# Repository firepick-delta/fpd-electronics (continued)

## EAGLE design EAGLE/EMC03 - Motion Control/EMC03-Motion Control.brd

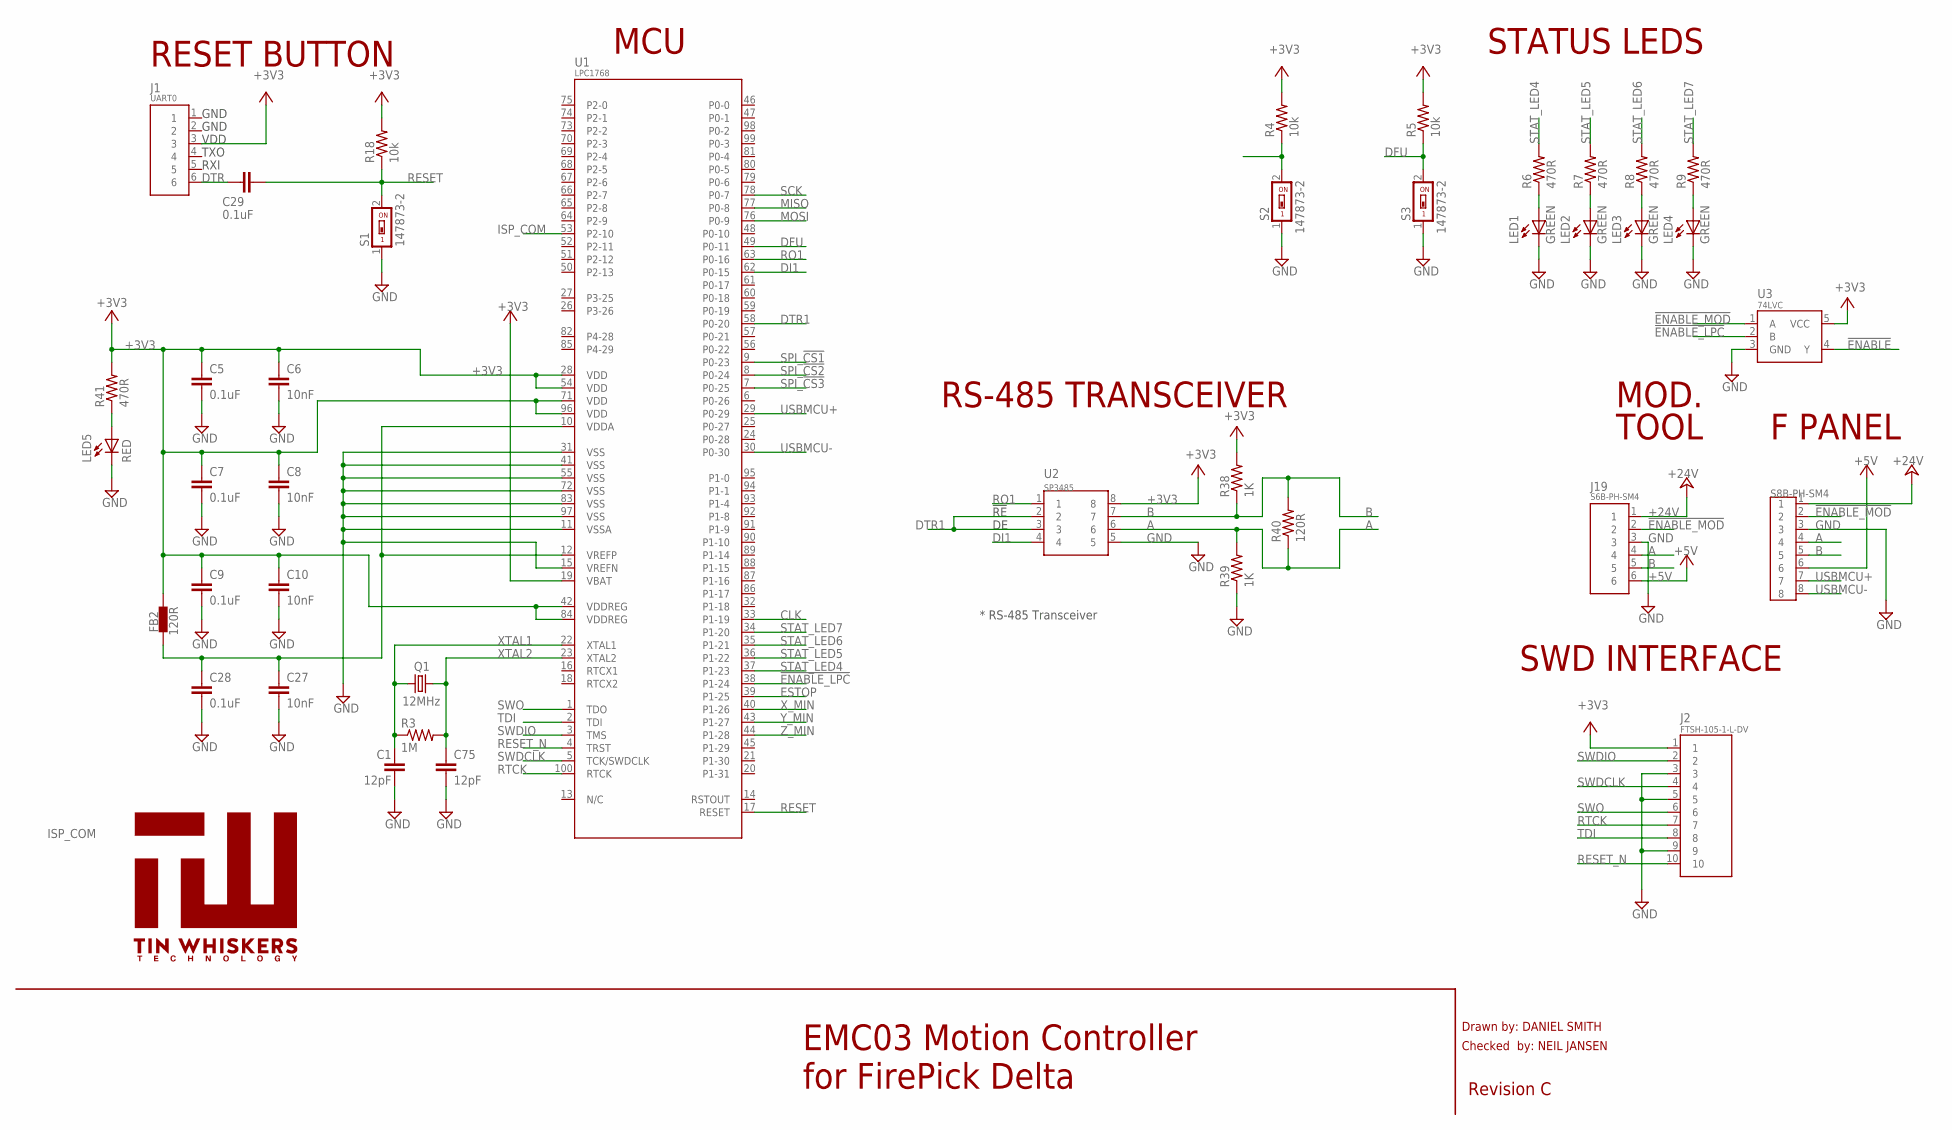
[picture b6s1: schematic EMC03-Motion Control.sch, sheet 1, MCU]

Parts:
C1, C75: 12pF; C0603; PARTNO GRM1885C1H120FA01J
C5, C7, C9, C28, C29: 0.1uF; C0603; PARTNO GMK107BJ104KAHT
C6, C8, C10, C27: 10nF; C0603; PARTNO GRM188R71H103KA01D
FB2: 120R; F0603; PARTNO BLM18AG121SN1D
J1: UART0; CON-HDR-6POS-MALE; PARTNO 67996-206HLF
J2: FTSH-105-1-L-DV; FTSH-105-01-XXX-DV-K; PARTNO FTSH-105-01-L-DV
J17: S8B-PH-SM4; CONN-JST-PH-2.0MM-8P-SMT-RA; PARTNO S8B-PH-SM4-TB(LF)(SN)
J19: S6B-PH-SM4; CONN-JST-PH-2.0MM-6P-SMT-RA; PARTNO S6B-PH-SM4-TB(LF)(SN)
LED1, LED2, LED3, LED4: GREEN; LED0603; PARTNO SML-D12M8WT86
LED5: RED; LED0603; PARTNO SML-D12U8WT86
Q1: 12MHz; HC-49/U-S; PARTNO HCM4912000000ABJT
R3: 1M; R0603; PARTNO RC0603FR-071ML
R4, R5, R18: 10k; R0603; PARTNO RC0603FR-0710KL
R6, R7, R8, R9, R41: 470R; R0603; PARTNO RC0603FR-07470RL
R38, R39: 1K; R0603; PARTNO RC0603FR-071KL
R40: 120R; R0603; PARTNO RC0805FR-07120RL
S1, S2, S3: 147873-2; PARTNO 147873-2
U1: LPC1768; 100-LQFP; PARTNO LPC1768
U2: SP3485; SOICN-8; PARTNO SP3485
U3: 74LVC; SOT-23-5; PARTNO SN74LVC1G32DBVR
U$1: TIN-WHISKERSSMALL; TIN-WHISKERS-SMALL; PARTNO *

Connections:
!ENABLE: U3.4 (Y); also elsewhere on the board
!ENABLE_LPC: U1.38 (P1-24), U3.2 (B)
!ENABLE_MOD: J17.2, J19.2, U3.1 (A)
+3V3: C5.2, C6.2, C7.2, C8.2, C9.2, C10.2, FB2.2, J1.3, J2.1, R4.2, R5.2, R18.2, R38.2, R41.2, U1.19 (VBAT), U1.28 (VDD), U1.42 (VDDREG), U1.54 (VDD), U1.71 (VDD), U1.84 (VDDREG), U1.96 (VDD), U2.8, U3.5 (VCC); also elsewhere on the board
+5V: J17.6, J19.6; also elsewhere on the board
+24V: J17.1, J19.1; also elsewhere on the board
A: J17.4, J19.4, R39.2, R40.1, U2.6
B: J17.5, J19.5, R38.1, R40.2, U2.7
CLK: U1.33 (P1-19); also elsewhere on the board
DFU: R5.1, S3.2, U1.49 (P0-11)
DI1: U1.62 (P0-15), U2.4
DPWR: C27.2, C28.2, FB2.1, U1.10 (VDDA), U1.12 (VREFP)
DTR: C29.1, J1.6
DTR1: U1.58 (P0-20), U2.2, U2.3
ESTOP: U1.39 (P1-25)
GND: C1.1, C5.1, C6.1, C7.1, C8.1, C9.1, C10.1, C27.1, C28.1, C75.1, J2.3, J2.5, J2.9, J17.3, J19.3, LED1.C, LED2.C, LED3.C, LED4.C, LED5.C, R39.1, S1.1, S2.1, S3.1, U1.11 (VSSA), U1.15 (VREFN), U1.31 (VSS), U1.41 (VSS), U1.55 (VSS), U1.72 (VSS), U1.83 (VSS), U1.97 (VSS), U2.5, U3.3 (GND); also elsewhere on the board
ISP_COM: R4.1, S2.2, U1.53 (P2-10)
MISO: U1.77 (P0-8); also elsewhere on the board
MOSI: U1.76 (P0-9); also elsewhere on the board
unnamed: LED5.A, R41.1
unnamed: LED1.A, R6.1
unnamed: LED2.A, R7.1
unnamed: LED4.A, R9.1
unnamed: LED3.A, R8.1
RESET: C29.2, R18.1, S1.2, U1.17 (RESET)
RESET_N: J2.10, U1.4 (TRST)
RO1: U1.63 (P0-16), U2.1
RTCK: J2.7, U1.100 (RTCK)
SCK: U1.78 (P0-7); also elsewhere on the board
SPI_!CS1: U1.9 (P0-23); also elsewhere on the board
SPI_!CS2: U1.8 (P0-24); also elsewhere on the board
SPI_!CS3: U1.7 (P0-25); also elsewhere on the board
STAT_LED4: R6.2, U1.37 (P1-23)
STAT_LED5: R7.2, U1.36 (P1-22)
STAT_LED6: R8.2, U1.35 (P1-21)
STAT_LED7: R9.2, U1.34 (P1-20)
SWDCLK: J2.4, U1.5 (TCK/SWDCLK)
SWDIO: J2.2, U1.3 (TMS)
SWO: J2.6, U1.1 (TDO)
TDI: J2.8, U1.2 (TDI)
USBMCU+: J17.7, U1.29 (P0-29)
USBMCU-: J17.8, U1.30 (P0-30)
XTAL1: C1.2, Q1.1, R3.1, U1.22 (XTAL1)
XTAL2: C75.2, Q1.2, R3.2, U1.23 (XTAL2)
X_MIN: U1.40 (P1-26); also elsewhere on the board
Y_MIN: U1.43 (P1-27); also elsewhere on the board
Z_MIN: U1.44 (P1-28); also elsewhere on the board

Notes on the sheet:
VDD
Drawn by: DANIEL SMITH
Checked by: NEIL JANSEN
Revision C
EMC03 Motion Controller for FirePick Delta
GND
TXO
RXI
STATUS LEDS
RESET BUTTON
MCU
MOD.
TOOL
!RE
* RS-485 Transceiver
RS-485 TRANSCEIVER
SWD INTERFACE
F PANEL

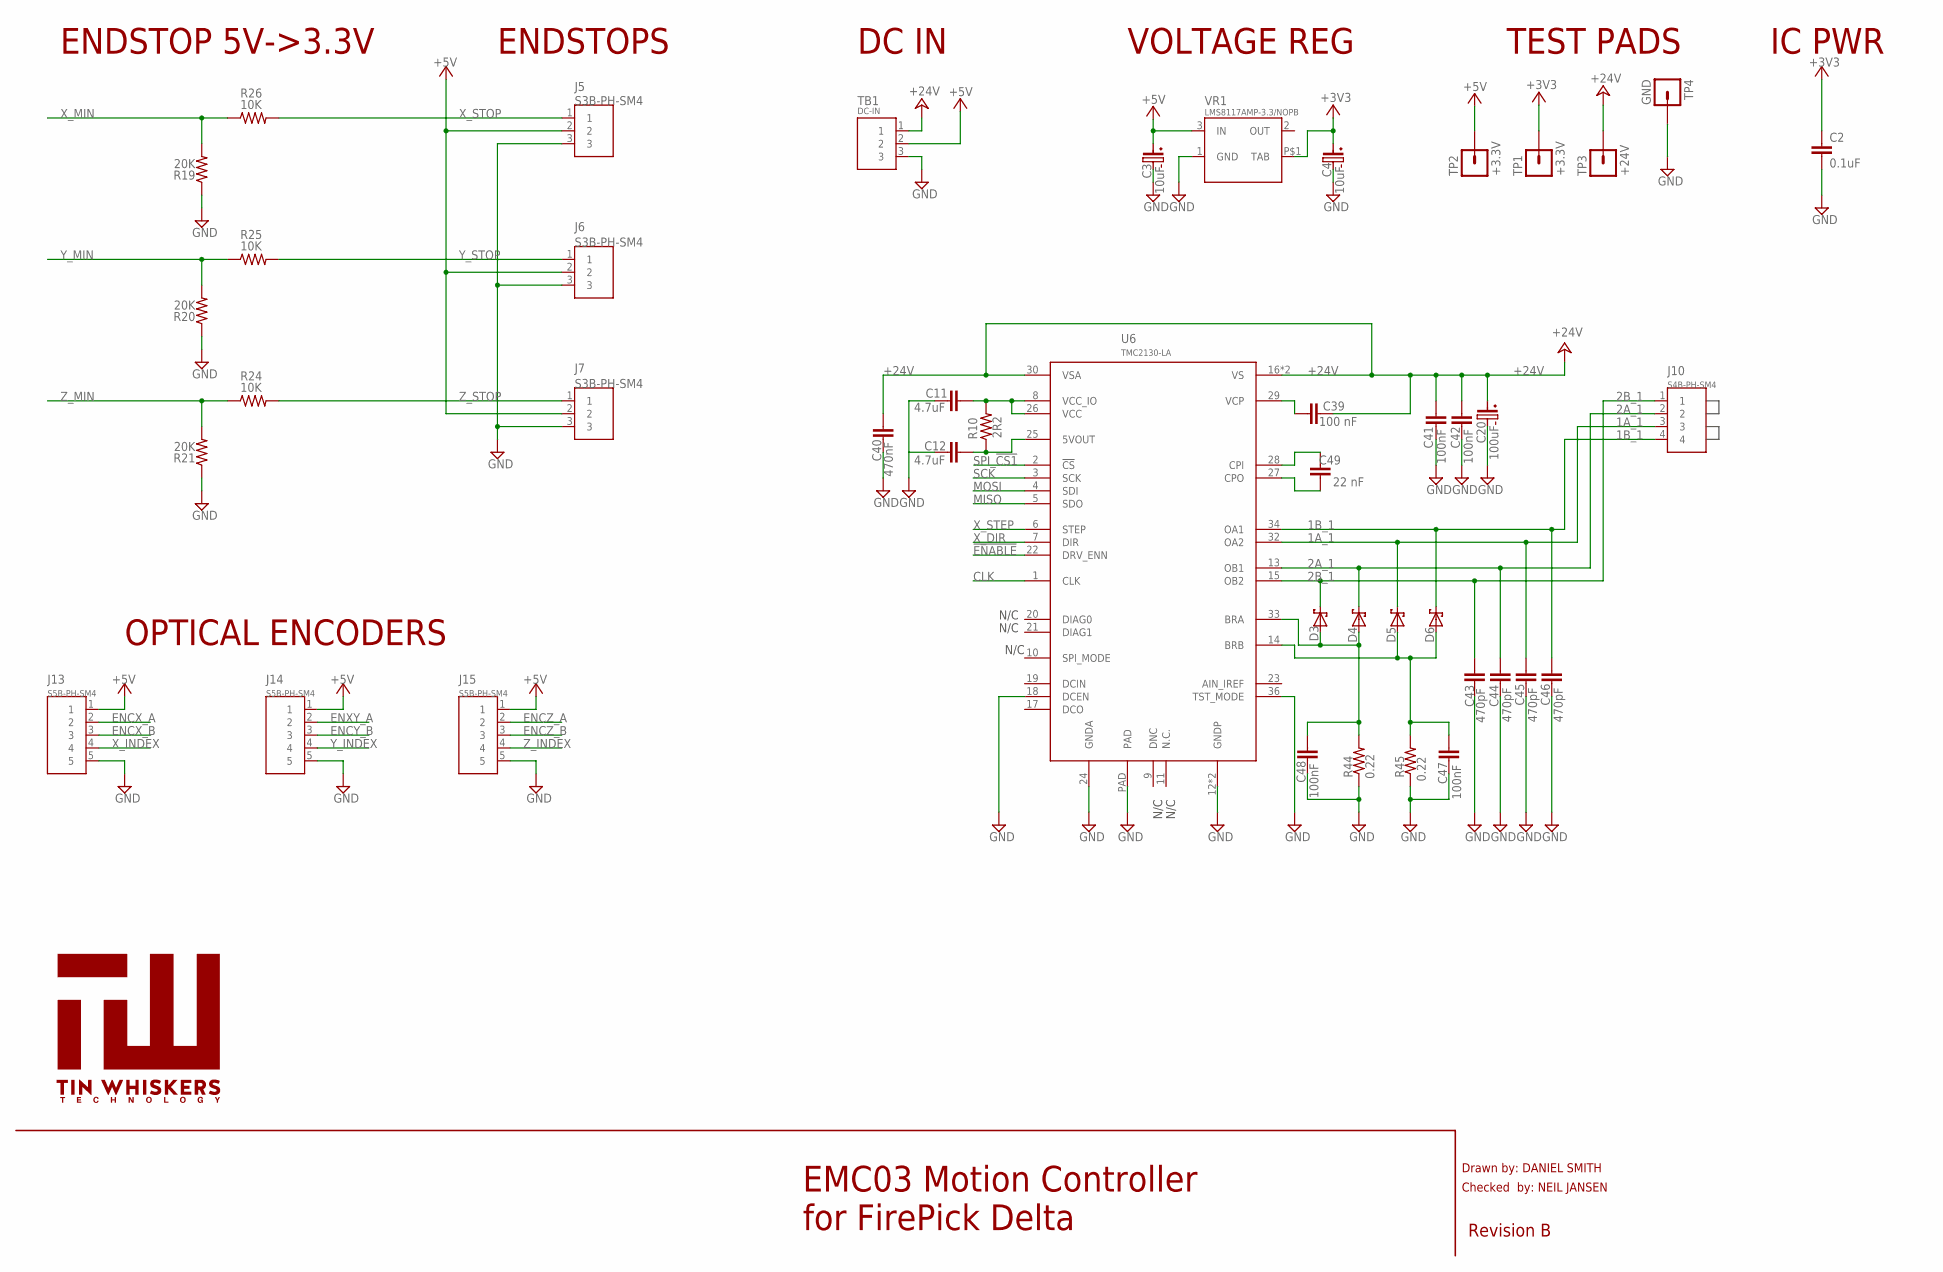
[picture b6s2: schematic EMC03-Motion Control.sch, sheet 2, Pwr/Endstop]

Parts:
C2: 0.1uF; C0603; PARTNO UMK107B7104KA-T
C3, C4: 10uF; C-SMD-6.3MM; PARTNO EMVH350ADA100MF60G
C11, C12: 4.7uF; C0603; PARTNO GRM188C81E475KE11D
C20: 100uF; C-SMD-6.3MM; PARTNO EEE-FTH101XAP
C39: 100 nF; C0603; PARTNO UMK107B7104KA-T
C40: 470nF; C0603; PARTNO UMK107B7474KA-TR
C41, C42, C47, C48: 100nF; C0603; PARTNO UMK107B7104KA-T
C43, C44, C45, C46: 470pF; C0603; PARTNO GRM188R72A471KA01D
C49: 22 nF; C0603; PARTNO GRM188R71H223KA01D
D3, D4, D5, D6: MSS1P6; MICRO-SMP; PARTNO MSS1P6
J5, J6, J7: S3B-PH-SM4; CONN-JST-PH-2.0MM-3P-SMT-RA; PARTNO S3B-PH-SM4-TB(LF)(SN)
J10: S4B-PH-SM4; CONN-JST-PH-2.0MM-4P-SMT-RA; PARTNO S4B-PH-SM4-TB(LF)(SN)
J13, J14, J15: S5B-PH-SM4; CONN-JST-PH-2.0MM-5P-SMT-RA; PARTNO S5B-PH-SM4-TB(LF)(SN)
R10: 2R2; R0603; PARTNO RC0603FR-072R2L
R19, R20, R21: 20K; R0603; PARTNO RC0603FR-0720KL
R24, R25, R26: 10K; R0603; PARTNO RC0603FR-0710KL
R44, R45: 0.22; R1206; PARTNO RL1206FR-7W0R22L
TB1: DC-IN; TBLOCK-3-5MM-OSTTH030160; PARTNO OSTTH030160
TP1, TP2: +3.3V; TESTPAD; PARTNO N/A
TP3: +24V; TESTPAD; PARTNO N/A
TP4: GND; TESTPAD; PARTNO N/A
U6: TMC2130-LA; 36-QFN(5X6); PARTNO TMC2130-LA
U$2: TIN-WHISKERSSMALL; TIN-WHISKERS-SMALL; PARTNO *
VR1: LMS8117AMP-3.3/NOPB; SOT-223; PARTNO LMS8117AMP-3.3/NOPB

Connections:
1A_1: C45.1, D5.NEG (C), J10.3, U6.32 (OA2)
1B_1: C46.1, D6.NEG (C), J10.4, U6.34 (OA1)
2A_1: C44.1, D4.NEG (C), J10.2, U6.13 (OB1)
2B_1: C43.1, D3.NEG (C), J10.1, U6.15 (OB2)
!ENABLE: U6.22 (DRV_ENN); also elsewhere on the board
+3V3: C2.1, C4.POS, TP1.PAD, VR1.P$1 (TAB); also elsewhere on the board
+5V: C3.POS, J5.2, J6.2, J7.2, J13.1, J14.1, J15.1, TB1.2, TP2.PAD, VR1.3 (IN); also elsewhere on the board
+24V: C20.POS, C39.2, C40.2, C41.1, C42.1, TB1.1, TP3.PAD, U6.16 (VS), U6.30 (VSA), U6.31 (VS); also elsewhere on the board
BRA: C48.1, D3.POS (A), D4.POS (A), R44.2, U6.33 (BRA)
BRB: C47.1, D5.POS (A), D6.POS (A), R45.2, U6.14 (BRB)
CLK: U6.1 (CLK); also elsewhere on the board
CPI: C49.2, U6.28 (CPI)
CPO: C49.1, U6.27 (CPO)
ENCX_A: J13.2
ENCX_B: J13.3
ENCY_B: J14.3
ENCZ_A: J15.2
ENCZ_B: J15.3
ENXY_A: J14.2
GND: C2.2, C3.NEG, C4.NEG, C11.1, C12.1, C20.NEG, C40.1, C41.2, C42.2, C43.2, C44.2, C45.2, C46.2, C47.2, C48.2, J5.3, J6.3, J7.3, J13.5, J14.5, J15.5, R19.1, R20.1, R21.1, R44.1, R45.1, TB1.3, TP4.PAD, U6.12 (GNDP), U6.18 (DCEN), U6.24 (GNDA), U6.35 (GNDP), U6.36 (TST_MODE), U6.PAD, VR1.1 (GND); also elsewhere on the board
MISO: U6.5 (SDO); also elsewhere on the board
MOSI: U6.4 (SDI); also elsewhere on the board
unnamed: C11.2, R10.2, U6.8 (VCC_IO), U6.26 (VCC)
unnamed: C12.2, R10.1, U6.25 (5VOUT)
SCK: U6.3 (SCK); also elsewhere on the board
SPI_!CS1: U6.2 (!CS); also elsewhere on the board
VCP: C39.1, U6.29 (VCP)
X_DIR: U6.7 (DIR)
X_INDEX: J13.4
X_MIN: R19.2, R26.1; also elsewhere on the board
X_STEP: U6.6 (STEP)
X_STOP: J5.1, R26.2
Y_INDEX: J14.4
Y_MIN: R20.2, R25.1; also elsewhere on the board
Y_STOP: J6.1, R25.2
Z_INDEX: J15.4
Z_MIN: R21.2, R24.1; also elsewhere on the board
Z_STOP: J7.1, R24.2

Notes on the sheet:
Drawn by: DANIEL SMITH
Checked by: NEIL JANSEN
Revision B
EMC03 Motion Controller for FirePick Delta
TEST PADS
ENDSTOP 5V->3.3V
ENDSTOPS
IC PWR
OPTICAL ENCODERS
VOLTAGE REG
DC IN
N/C

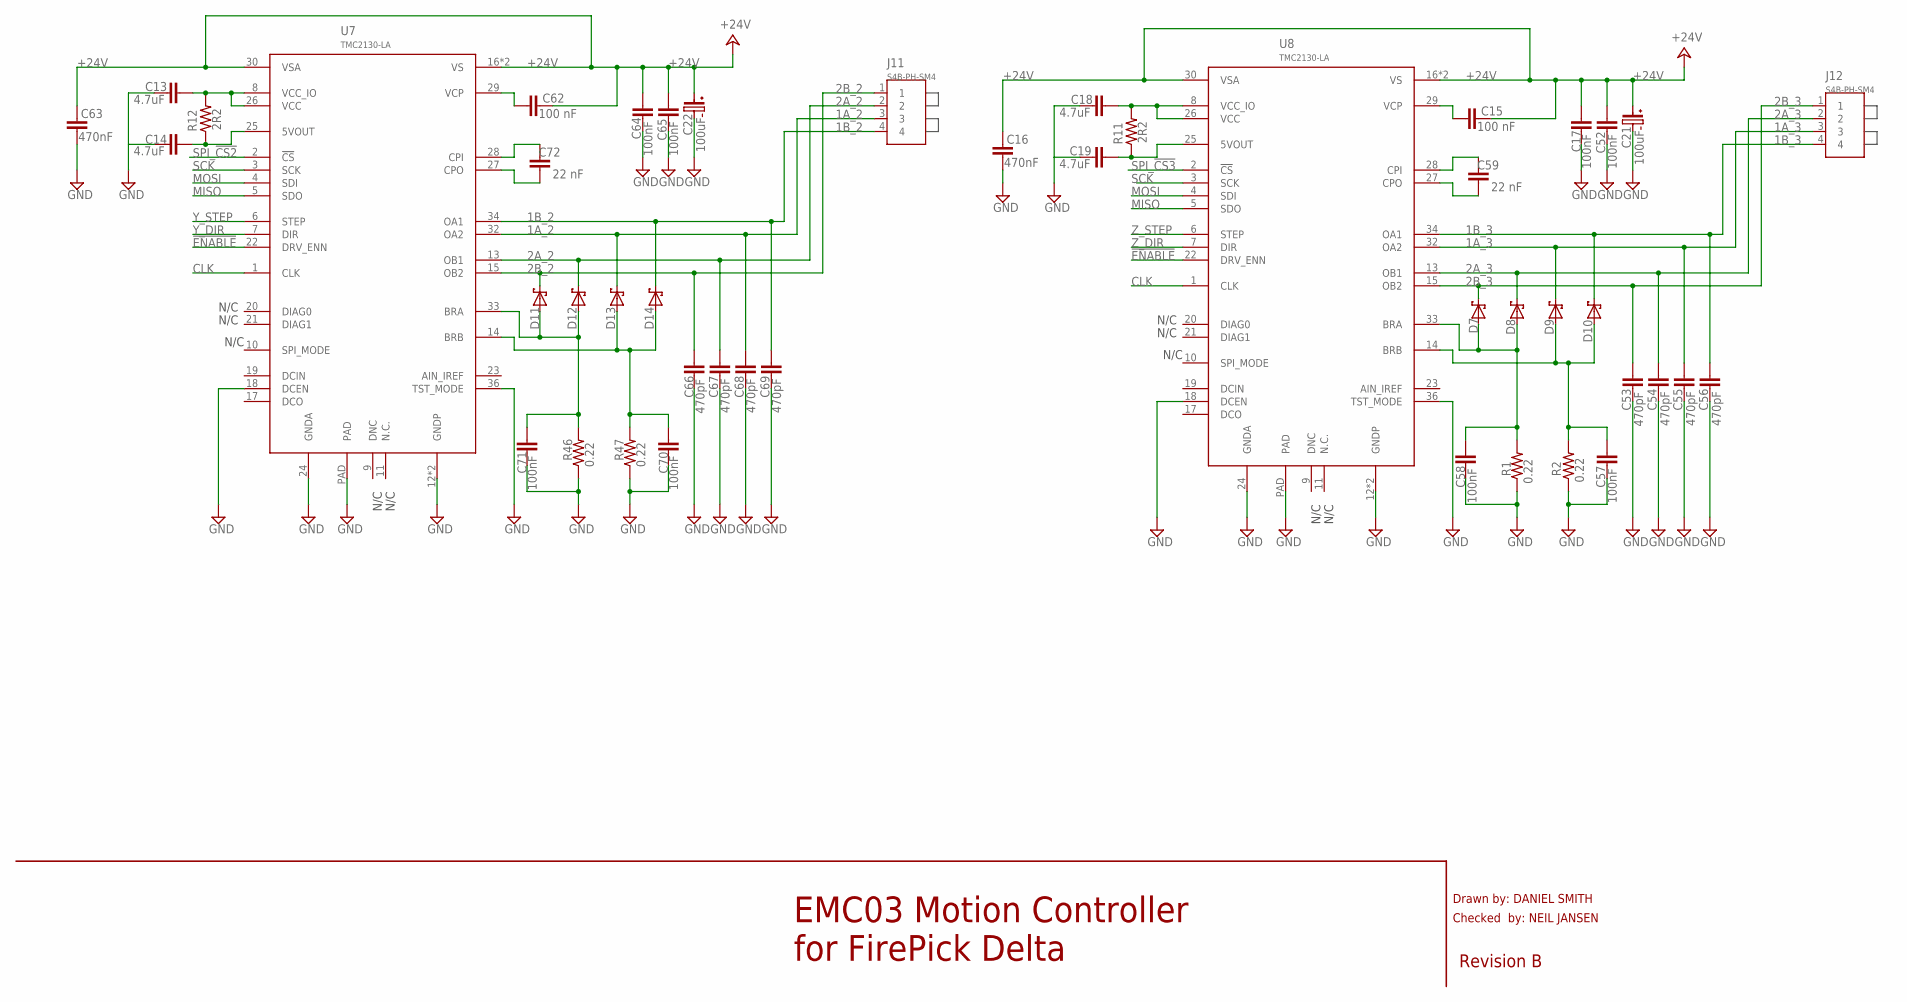
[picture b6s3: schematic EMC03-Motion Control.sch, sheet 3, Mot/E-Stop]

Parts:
C13, C14, C18, C19: 4.7uF; C0603; PARTNO GRM188C81E475KE11D
C15, C62: 100 nF; C0603; PARTNO UMK107B7104KA-T
C16, C63: 470nF; C0603; PARTNO UMK107B7474KA-TR
C17, C52, C57, C58, C64, C65, C70, C71: 100nF; C0603; PARTNO UMK107B7104KA-T
C21, C22: 100uF; C-SMD-6.3MM; PARTNO EEE-FTH101XAP
C53, C54, C55, C56, C66, C67, C68, C69: 470pF; C0603; PARTNO GRM188R72A471KA01D
C59, C72: 22 nF; C0603; PARTNO GRM188R71H223KA01D
D7, D8, D9, D10, D11, D12, D13, D14: MSS1P6; MICRO-SMP; PARTNO MSS1P6
J11, J12: S4B-PH-SM4; CONN-JST-PH-2.0MM-4P-SMT-RA; PARTNO S4B-PH-SM4-TB(LF)(SN)
R1, R2, R46, R47: 0.22; R1206; PARTNO RL1206FR-7W0R22L
R11, R12: 2R2; R0603; PARTNO RC0603FR-072R2L
U7, U8: TMC2130-LA; 36-QFN(5X6); PARTNO TMC2130-LA

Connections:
1A_2: C68.1, D13.NEG (C), J11.3, U7.32 (OA2)
1A_3: C55.1, D9.NEG (C), J12.3, U8.32 (OA2)
1B_2: C69.1, D14.NEG (C), J11.4, U7.34 (OA1)
1B_3: C56.1, D10.NEG (C), J12.4, U8.34 (OA1)
2A_2: C67.1, D12.NEG (C), J11.2, U7.13 (OB1)
2A_3: C54.1, D8.NEG (C), J12.2, U8.13 (OB1)
2B_2: C66.1, D11.NEG (C), J11.1, U7.15 (OB2)
2B_3: C53.1, D7.NEG (C), J12.1, U8.15 (OB2)
!ENABLE: U7.22 (DRV_ENN), U8.22 (DRV_ENN); also elsewhere on the board
+24V: C15.2, C16.2, C17.1, C21.POS, C22.POS, C52.1, C62.2, C63.2, C64.1, C65.1, U7.16 (VS), U7.30 (VSA), U7.31 (VS), U8.16 (VS), U8.30 (VSA), U8.31 (VS); also elsewhere on the board
BRA2: C71.1, D11.POS (A), D12.POS (A), R46.2, U7.33 (BRA)
BRA3: C58.1, D7.POS (A), D8.POS (A), R1.2, U8.33 (BRA)
BRB2: C70.1, D13.POS (A), D14.POS (A), R47.2, U7.14 (BRB)
BRB3: C57.1, D9.POS (A), D10.POS (A), R2.2, U8.14 (BRB)
CLK: U7.1 (CLK), U8.1 (CLK); also elsewhere on the board
CPI1: C59.2, U8.28 (CPI)
CPI2: C72.2, U7.28 (CPI)
CPO1: C59.1, U8.27 (CPO)
CPO2: C72.1, U7.27 (CPO)
GND: C13.1, C14.1, C16.1, C17.2, C18.1, C19.1, C21.NEG, C22.NEG, C52.2, C53.2, C54.2, C55.2, C56.2, C57.2, C58.2, C63.1, C64.2, C65.2, C66.2, C67.2, C68.2, C69.2, C70.2, C71.2, R1.1, R2.1, R46.1, R47.1, U7.12 (GNDP), U7.18 (DCEN), U7.24 (GNDA), U7.35 (GNDP), U7.36 (TST_MODE), U7.PAD, U8.12 (GNDP), U8.18 (DCEN), U8.24 (GNDA), U8.35 (GNDP), U8.36 (TST_MODE), U8.PAD; also elsewhere on the board
MISO: U7.5 (SDO), U8.5 (SDO); also elsewhere on the board
MOSI: U7.4 (SDI), U8.4 (SDI); also elsewhere on the board
unnamed: C19.2, R11.1, U8.25 (5VOUT)
unnamed: C18.2, R11.2, U8.8 (VCC_IO), U8.26 (VCC)
unnamed: C14.2, R12.1, U7.25 (5VOUT)
unnamed: C13.2, R12.2, U7.8 (VCC_IO), U7.26 (VCC)
SCK: U7.3 (SCK), U8.3 (SCK); also elsewhere on the board
SPI_!CS2: U7.2 (!CS); also elsewhere on the board
SPI_!CS3: U8.2 (!CS); also elsewhere on the board
VCP1: C15.1, U8.29 (VCP)
VCP2: C62.1, U7.29 (VCP)
Y_DIR: U7.7 (DIR)
Y_STEP: U7.6 (STEP)
Z_DIR: U8.7 (DIR)
Z_STEP: U8.6 (STEP)

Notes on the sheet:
Drawn by: DANIEL SMITH
Checked by: NEIL JANSEN
Revision B
EMC03 Motion Controller for FirePick Delta
N/C

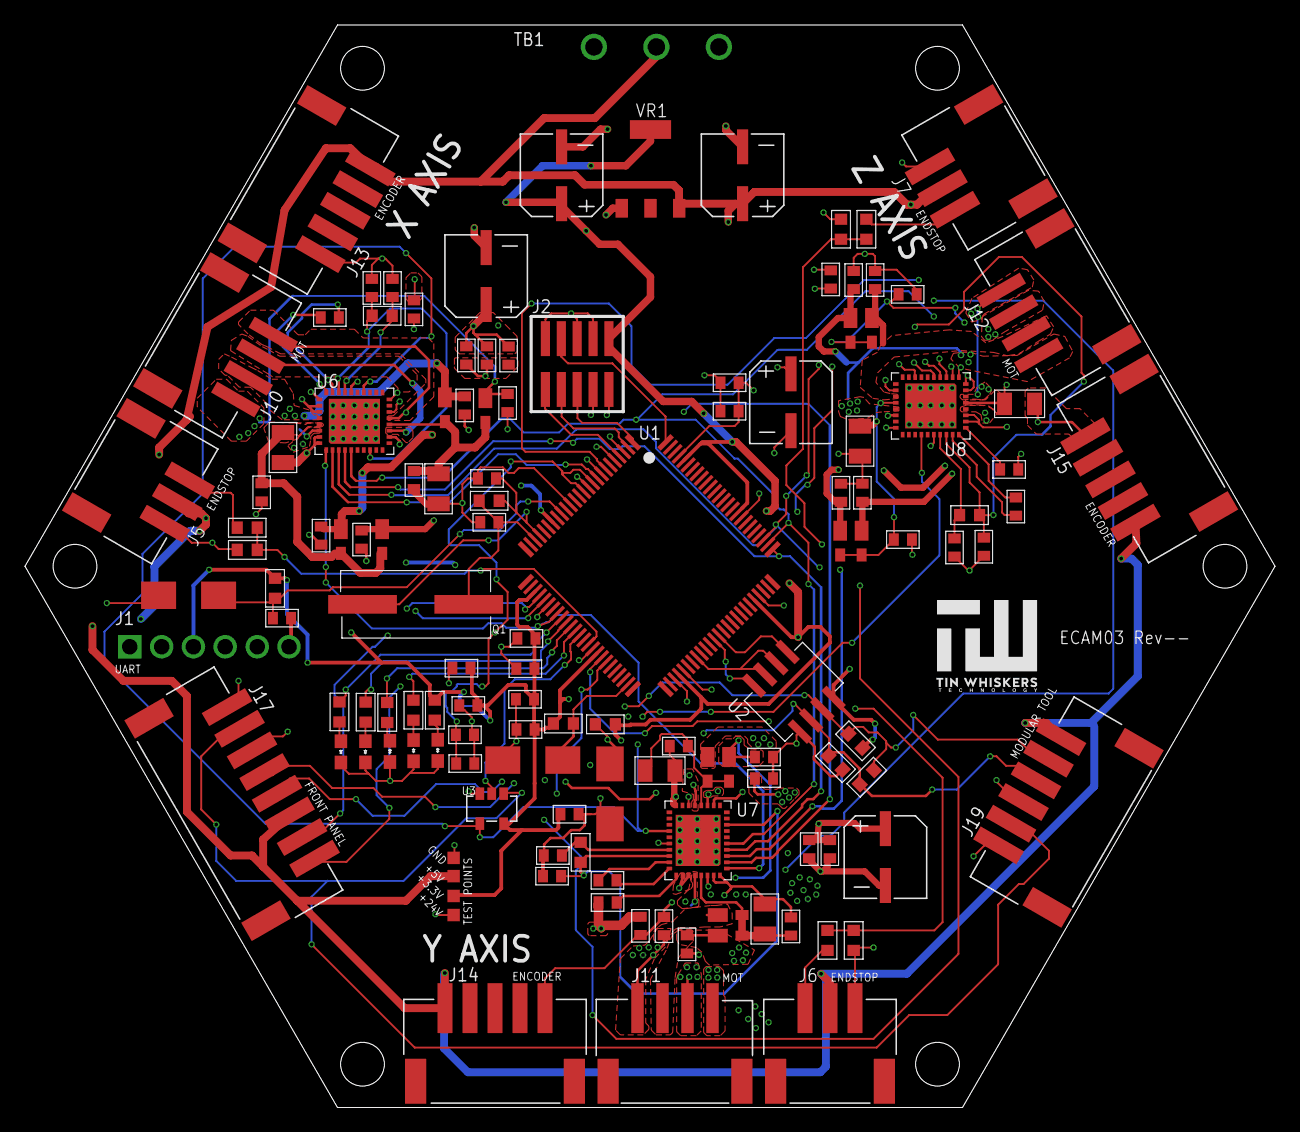
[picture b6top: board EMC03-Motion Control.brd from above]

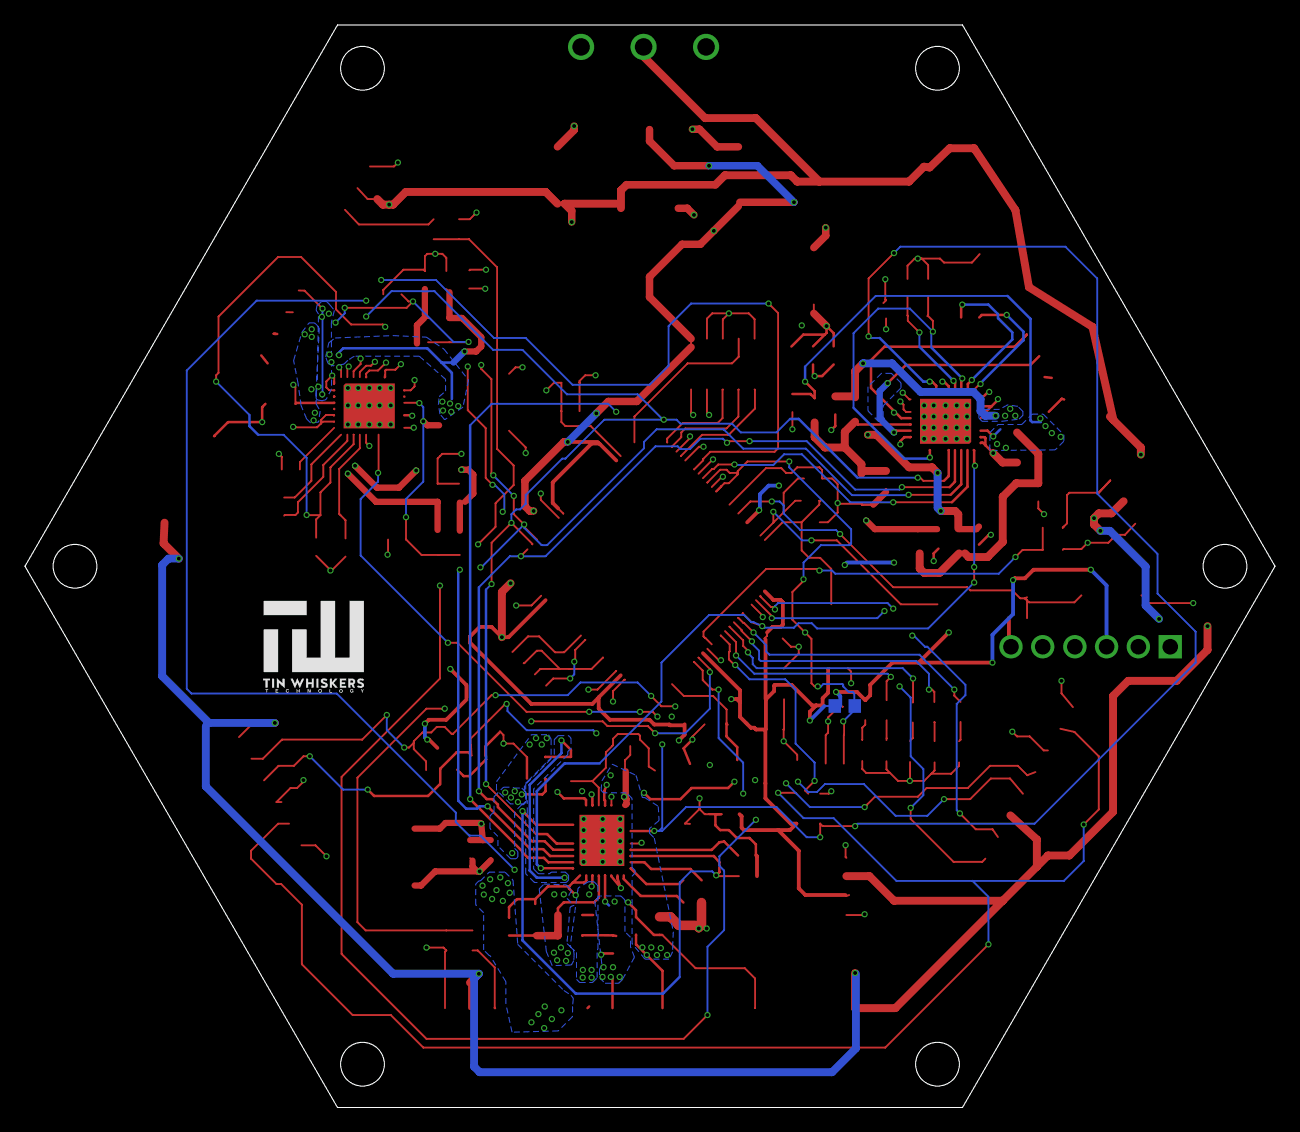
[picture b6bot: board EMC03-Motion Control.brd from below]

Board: 4 copper layers, 100.0 x 86.6 mm, 132 parts (2 on the bottom side), 82 nets.

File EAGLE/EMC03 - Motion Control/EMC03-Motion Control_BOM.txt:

Part No.	Description	Part References	Qty-1	Mfg Name	Distr.	Price(USD):	Status:	Notes:
EMC03	Motion Controller PCB	EMC03	-	Tin Whiskers Technology	N/A	-	-	-
-	Bare PCB, FR-4, 0.062”, 4-Layer		1	HQPCB	N/A			
GMK107BJ104KAHT	Capacitor: 0.1uF, 35V, 10%, X5R	C2, C5, C7, C9, C28, C29	6	Taiyo Yuden	ANY			Change on SCH
RL1206FR-7W0R22L	Resistor: 0.22 Ohm, 0.5W, 1%	R1, R2, R44, R45, R46, R47	6	Yageo	ANY			
RC0603FR-071KL	Resistor: 1 kOhm, 0.1W, 1%	R38, R39	2	Yageo	ANY			
RC0603FR-071ML	Resistor: 1 Mohm, 0.1W, 5%	R3	1	Yageo	ANY			
RC0603FR-072R2L	Resistor: 2.2 Ohm, 0.1W, 1%	R10, R11, R12	3	Yageo	ANY			
GRM188C81E475KE11D	Capacitor: 4.7 uF, 25V, 10%, X6S	C11, C12, C13, C14, C18, C19	6	Murata	ANY			
RC0603FR-0710KL	Resistor: 10 kOhm, 0.1W, 1%	R24, R25, R26, R4, R5, R18	6	Yageo	ANY			
GRM188R71H103KA01D	Capacitor: 10nF, 50V, 10%, X7R	C6, C8, C10, C27	4	Murata	ANY			
EMVH350ADA100MF60G	Capacitor, AL-Electrolytic, 10uF, 35V, 20%	C3, C4	2	United Chemi-Con	ANY			
HCM4912000000ABJT	Crystal Oscillator: 12MHz, 18pF, 30PPM	Q1	1	Citizen FM	ANY			
GRM1885C1H120FA01J	Capacitor: 12pF, 50V, 1%, C0G	C1, C75	2	Murata	ANY			
RC0603FR-0722KL	Resistor: 20 kOhm, 0.1W, 5%	R19, R20, R21	3	Yageo	ANY			
GRM188R71H223KA01D	Capacitor: 22nF, 50V, 10%	C49, C59, C72	3	United Chemi-Con	ANY			
SN74LVC1G32DBVR	Logic Gate: OR, 1-CH, SOT23-5	U3	1	Texas Instruments	ANY			
UMK107B7104KA-T	Capacitor: 0.1uF, 50V, 10%, X7R	C15, C39, C62, C47, C48, C57, C58, C70, C71, C17, C41, C42, C52, C64, C65	15	Taiyo Yuden	ANY			Check Voltage Ratings
EEE-FTH101XAP	Capacitor: 100 uF, Al-Elec., 20%, 50V, SMT	C20, C21, C22	3	Panasonic	ANY			
BLM18AG121SN1D	Ferrite Bead, Filter	FB2	1	Murata	ANY			
RC0805FR-07120RL	RES SMD 120 OHM 1% 1/8W 0805	R40	1	Yageo	ANY			
RC0603FR-07470RL	Resistor: 470 Ohm, 0.1W, 1%	R6, R7, R8, R9, R41	5	Yageo	ANY			
UMK107B7474KA-TR	Capacitor, 470nF, 50V, 10%, X7R	C16, C40, C63	3	Taiyo Yuden	ANY			
GRM188R72A471KA01D	Capacitor: 470pF, 100V, 10%, X7R	C43, C44, C45, C46, C53, C54, C55, C56, C66, C67, C68, C69	12	Murata	ANY			
147873-2	Switch: Push-button, Mom. NO	S2, S3	2	Alcoswitch	ANY			
CHS-01TA	SMD Dip Switch 1 pol.	S1	1	Copal Electronics	ANY			
OSTTH030160	TERM BLOCK PLUG 3POS 90DEG 5MM	TB1	1	On Shore Technology Inc	ANY			
FTSH-105-01-L-DV	Connector: Header, 0.05ﾔ, 10-Pin, Male, SMT	J2	1	Samtec	ANY			
SML-D12M8WT86	LED: YW/GN, Diffused, 2.2V, 20mA	LED1, LED2, LED3, LED4	4	Rohm	ANY			
LMS8117AMP-3.3/NOPB	Voltage Reg(LDO): Vi=15V, Vo=3.3V, I=1A	VR1	1	Texas Instruments	ANY			
LPC1768	Microprocessor: ARM Cortex-M3	U1	1	NXP	ANY			
MSS1P6	Diode: Rectifier, 1A, 60V	D3, D4, D5, D6, D7, D8, D9, D10, D11, D12, D13, D14	12	Vishay	ANY			
SML-D12U8WT86	LED: RD, Diffused, 2.2v 20mA	LED5	1	Rohm	ANY			
S3B-PH-SM4-TB(LF)(SN)	Connector: 2.0mm (JST), SMT, R/A, 3-POS(M)	J5, J6, J7	3	JST	ANY			
S4B-PH-SM4-TB(LF)(SN)	Connector: 2.0mm (JST), SMT, R/A, 4-POS(M)	J10, J11, J12	3	JST	ANY			
S5B-PH-SM4-TB(LF)(SN)	Connector: 2.0mm (JST), SMT, R/A, 5-POS(M)	J13, J14, J15	3	JST	ANY			
S6B-PH-SM4-TB(LF)(SN)	Connector: 2.0mm (JST), SMT, R/A, 6-POS(M)	J19	1	JST	ANY			
S8B-PH-SM4-TB(LF)(SN)	Connector: 2.0mm (JST), SMT, R/A, 8-POS(M)	J17	1	JST	ANY			
SP3485	Transceiver: RS-485 Chip	U2	1	EXAR	ANY			
TMC2130-LA	Stepper Driver (Trinamic TMC2130-LA)	U6, U7, U8	3	Trinamic	ANY			
67996-206HLF	Connector: Header, 0.1”, 6-Pin, Male, Thru-Hole	J1	1	FCI	ANY

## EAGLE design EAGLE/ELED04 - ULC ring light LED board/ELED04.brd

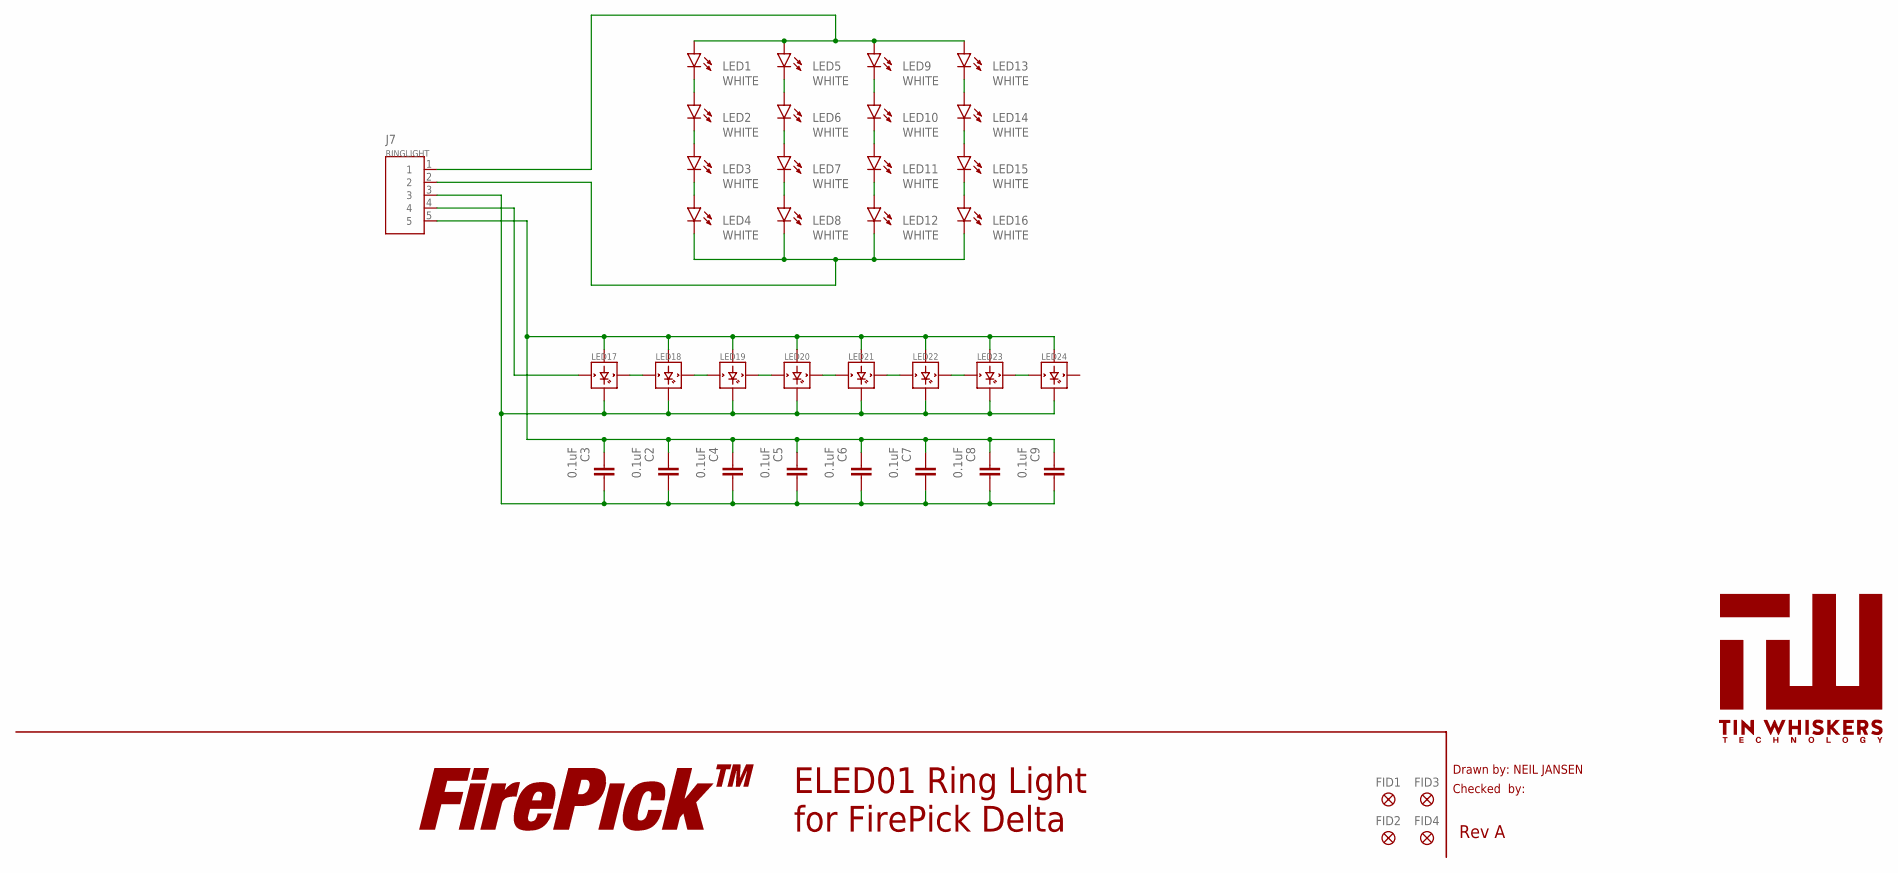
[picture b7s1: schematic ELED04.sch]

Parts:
C2, C3, C4, C5, C6, C7, C8, C9: 0.1uF; C0603; PARTNO GMK107BJ104KAHT
FID1, FID2, FID3, FID4: FIDUCIAL; PARTNO *
J7: RINGLIGHT; CON-JST-PH-2.0MM-5P-SMT-VRT; PARTNO B5B-PH-SM4-TB(LF)(SN)
LED1, LED2, LED3, LED4, LED5, LED6, LED7, LED8, LED9, LED10, LED11, LED12, LED13, LED14, LED15, LED16: WHITE; DIODE-1210; PARTNO QBLP650-IW
LED17, LED18, LED19, LED20, LED21, LED22, LED23, LED24: WS2812B; PARTNO 1655
LOGO4: LOGO-FIREPICKMEDIUM; LOGO-FIREPICK-MEDIUM
U$3: TIN-WHISKERSSMALL; TIN-WHISKERS-SMALL; PARTNO *

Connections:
+5V: C2.1, C3.1, C4.1, C5.1, C6.1, C7.1, C8.1, C9.1, J7.5, LED17.1-VDD (VDD), LED18.1-VDD (VDD), LED19.1-VDD (VDD), LED20.1-VDD (VDD), LED21.1-VDD (VDD), LED22.1-VDD (VDD), LED23.1-VDD (VDD), LED24.1-VDD (VDD)
GND: C2.2, C3.2, C4.2, C5.2, C6.2, C7.2, C8.2, C9.2, J7.3, LED17.3-GND (GND), LED18.3-GND (GND), LED19.3-GND (GND), LED20.3-GND (GND), LED21.3-GND (GND), LED22.3-GND (GND), LED23.3-GND (GND), LED24.3-GND (GND)
LED+: J7.1, LED1.A, LED5.A, LED9.A, LED13.A
LED-: J7.2, LED4.K (C), LED8.K (C), LED12.K (C), LED16.K (C)
unnamed: LED1.K (C), LED2.A
unnamed: LED17.2-DOUT (DOUT), LED18.4-DIN (DIN)
unnamed: LED3.K (C), LED4.A
unnamed: LED7.K (C), LED8.A
unnamed: LED18.2-DOUT (DOUT), LED19.4-DIN (DIN)
unnamed: LED2.K (C), LED3.A
unnamed: LED6.K (C), LED7.A
unnamed: LED10.K (C), LED11.A
unnamed: LED14.K (C), LED15.A
unnamed: LED19.2-DOUT (DOUT), LED20.4-DIN (DIN)
unnamed: LED20.2-DOUT (DOUT), LED21.4-DIN (DIN)
unnamed: LED9.K (C), LED10.A
unnamed: LED5.K (C), LED6.A
unnamed: LED11.K (C), LED12.A
unnamed: LED21.2-DOUT (DOUT), LED22.4-DIN (DIN)
unnamed: LED22.2-DOUT (DOUT), LED23.4-DIN (DIN)
unnamed: LED13.K (C), LED14.A
unnamed: LED23.2-DOUT (DOUT), LED24.4-DIN (DIN)
unnamed: LED15.K (C), LED16.A
unnamed: J7.4, LED17.4-DIN (DIN)

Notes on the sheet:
Drawn by: NEIL JANSEN
Checked by:
Rev A
ELED01 Ring Light for FirePick Delta

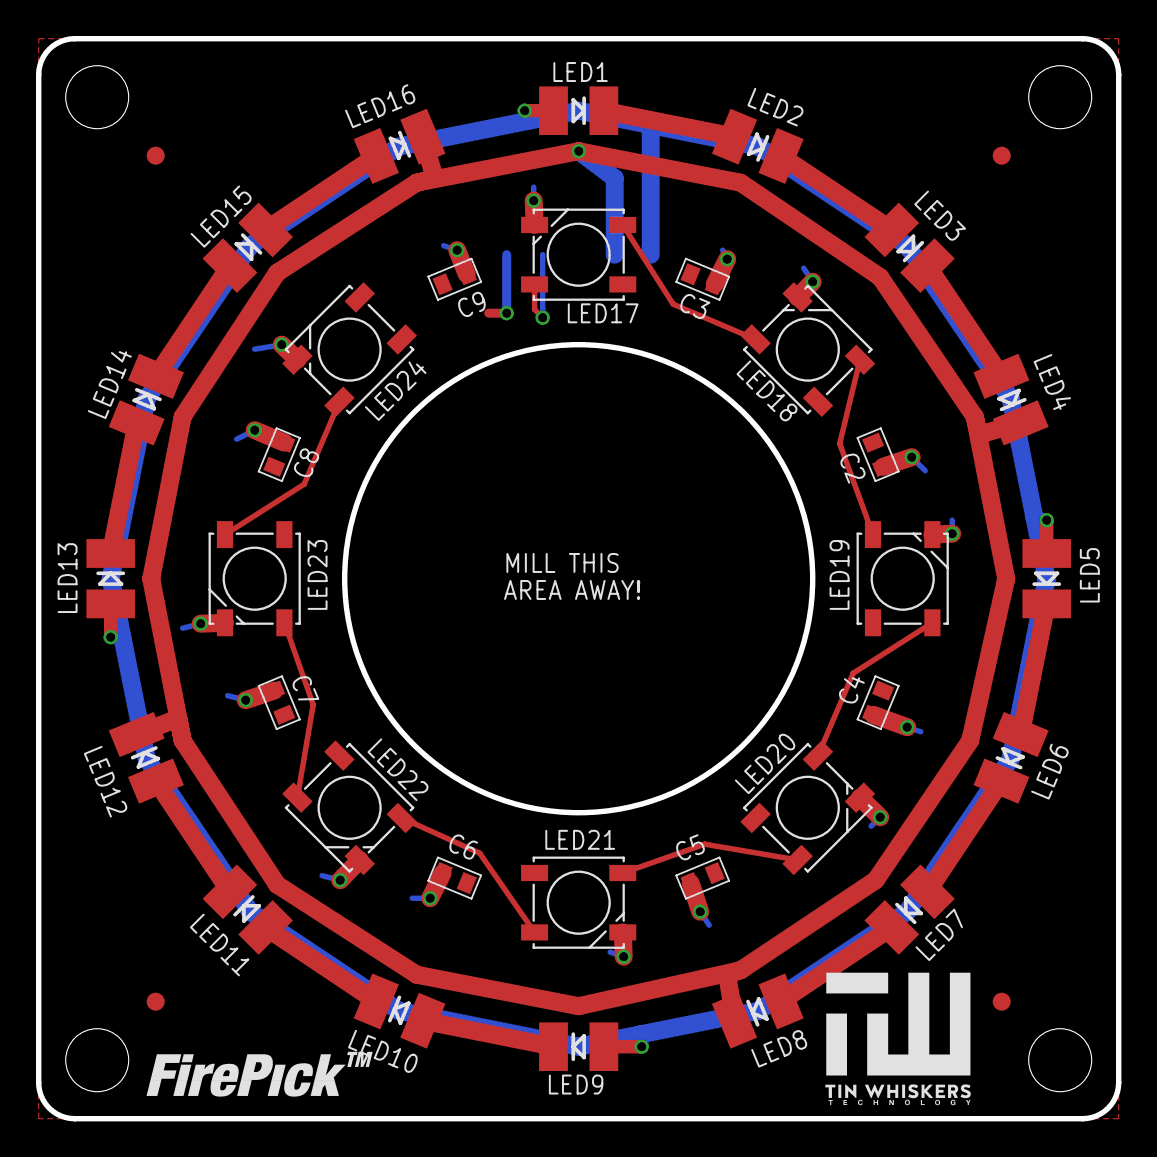
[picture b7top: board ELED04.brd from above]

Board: 2 copper layers, 60.0 x 60.0 mm, 39 parts (1 on the bottom side), 24 nets.
